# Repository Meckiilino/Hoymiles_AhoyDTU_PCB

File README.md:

# Hoymiles_AhoyDTU_PCB
KiCAD generated PCB to Stack D1 mini and NRF24L01+ module

PCB for AhoyDTU Project https://ahoydtu.de / https://github.com/lumapu/ahoy

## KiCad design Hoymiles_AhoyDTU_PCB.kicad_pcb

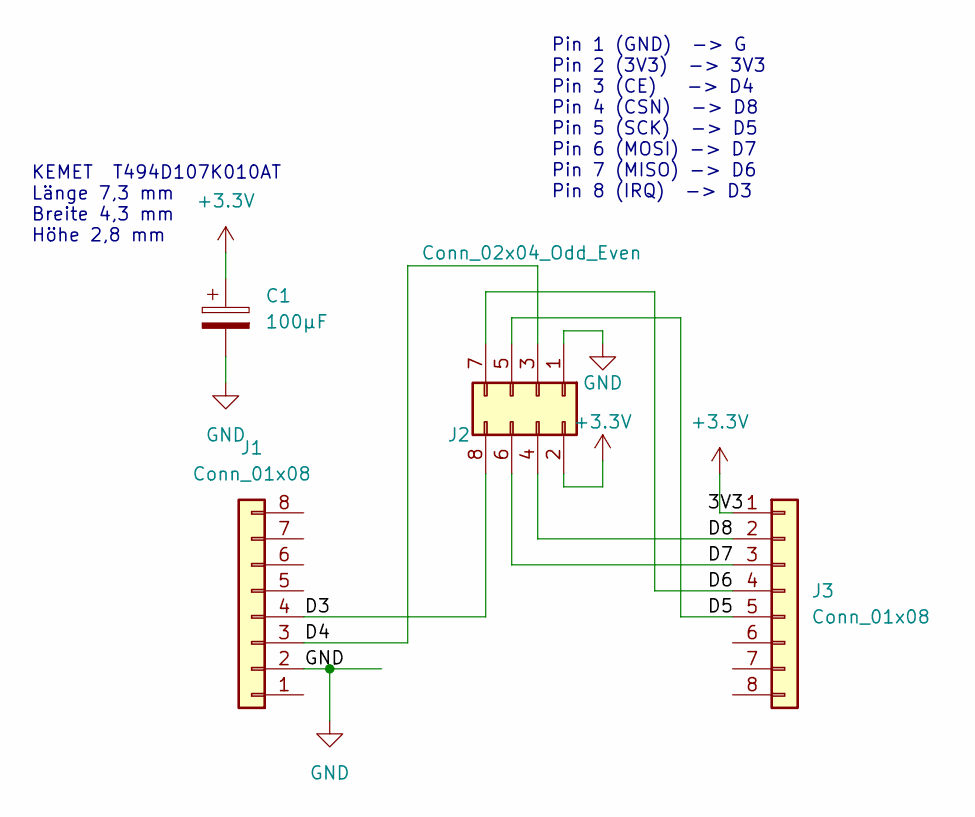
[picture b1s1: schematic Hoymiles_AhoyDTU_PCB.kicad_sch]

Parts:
C1: 100µF; C_Radial_D6.3mm_H7.0mm_P2.50mm
J1, J3: Conn_01x08; Connector_1x08_P2.54mm
J2: Conn_02x04_Odd_Even; Connector_2x04_P2.54mm

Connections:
+3V3: C1.1, J2.2, J3.1
/D3: J1.4, J2.8
/D4: J1.3, J2.3
/D5: J2.5, J3.5
/D6: J2.7, J3.4
/D7: J2.6, J3.3
/D8: J2.4, J3.2
GND: C1.2, J1.2, J2.1

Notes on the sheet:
KEMET T494D107K010AT Länge 7,3 mm Breite 4,3 mm Höhe 2,8 mm
Pin 1 (GND) -> G Pin 2 (3V3) -> 3V3 Pin 3 (CE) -> D4 Pin 4 (CSN) -> D8 Pin 5 (SCK) -> D5 Pin 6 (MOSI) -> D7 Pin 7 (MISO) -> D6 Pin 8 (IRQ) -> D3

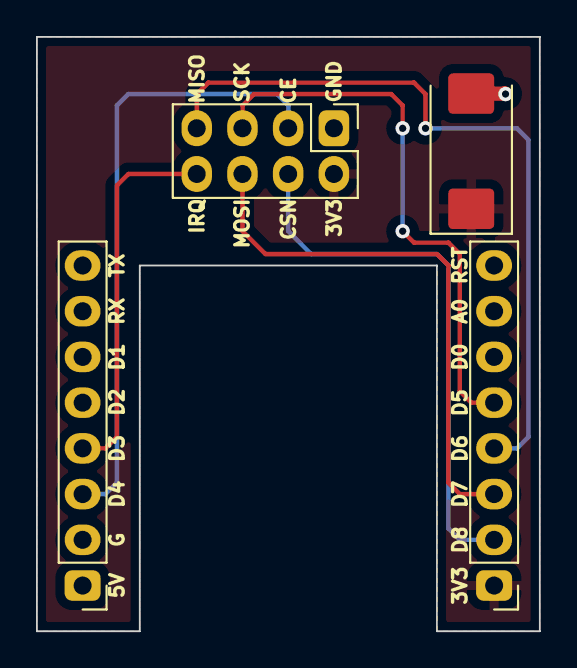
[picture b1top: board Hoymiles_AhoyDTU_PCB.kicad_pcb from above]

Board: 2 copper layers, 27.9 x 33.0 mm, 4 parts (0 on the bottom side), 8 nets.

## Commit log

2023-01-12 initial upload
2023-01-13 change to tantal capacitor
